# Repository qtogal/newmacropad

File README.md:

# newmacropad
This is my first macropad and my first time making a custom pcb. This macropad case comes with a stand so you can use it sort of like a stream deck. 

The case has a stand at the bottom, making the angle adjustable. 

# BOM
- 4x Cherry MX Switches
- 4x any Keycap
- 4x M3x5x4 Heatset inserts
- 4x M3x16mm SHCS Bolts
- 16x 1N4148 DO-35 Diodes.
- 1x 0.91" 128x32 OLED Display
- 1x XIAO RP2040
- 1x Case (2 prints, 1 of them have 3 print in place parts)

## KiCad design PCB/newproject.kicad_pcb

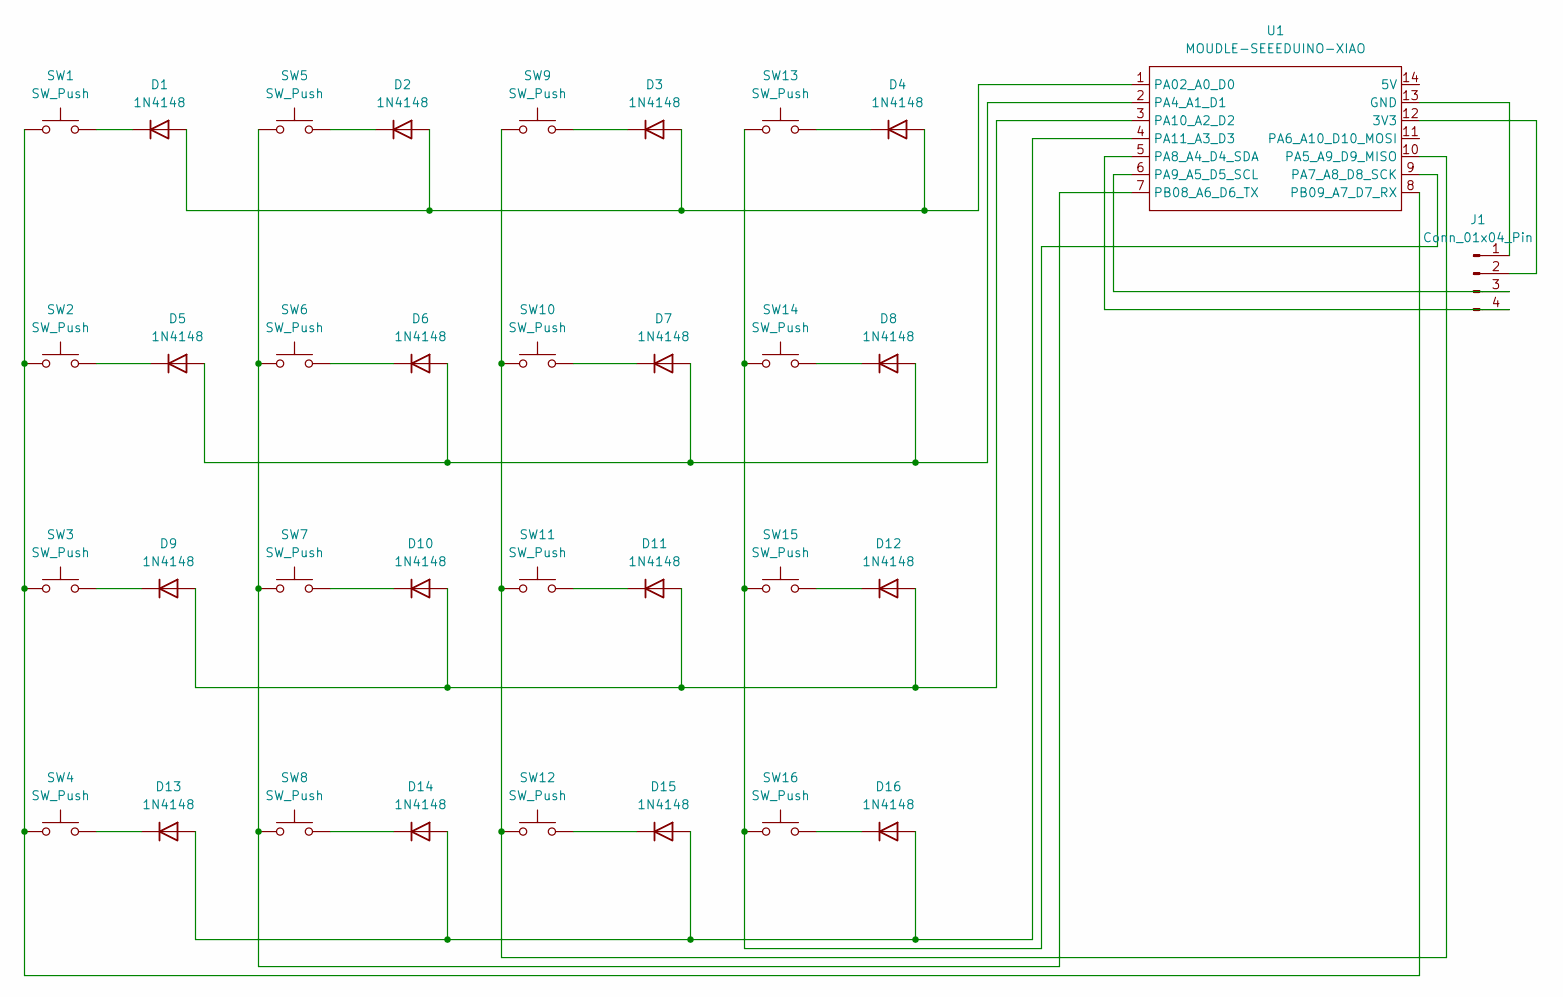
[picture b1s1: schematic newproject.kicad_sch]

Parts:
D1, D2, D3, D4, D5, D6, D7, D8, D9, D10, D11, D12, D13, D14, D15, D16: 1N4148; D_DO-35_SOD27_P7.62mm_Horizontal
J1: Conn_01x04_Pin; ER_OLEDM0.91_1x-I2C
SW1, SW2, SW3, SW4, SW5, SW6, SW7, SW8, SW9, SW10, SW11, SW12, SW13, SW14, SW15, SW16: SW_Push; SW_Cherry_MX_1.00u_PCB
U1: MOUDLE-SEEEDUINO-XIAO; XIAO-Generic-Hybrid-14P-2.54-21X17.8MM

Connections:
unnamed: D1.2 (A), D2.2 (A), D3.2 (A), D4.2 (A), U1.1 (PA02_A0_D0)
unnamed: D1.1 (K), SW1.2
unnamed: D2.1 (K), SW5.2
unnamed: D3.1 (K), SW9.2
unnamed: D4.1 (K), SW13.2
unnamed: D5.2 (A), D6.2 (A), D7.2 (A), D8.2 (A), U1.2 (PA4_A1_D1)
unnamed: D5.1 (K), SW2.2
unnamed: D6.1 (K), SW6.2
unnamed: D7.1 (K), SW10.2
unnamed: D8.1 (K), SW14.2
unnamed: D9.1 (K), SW3.2
unnamed: D9.2 (A), D10.2 (A), D11.2 (A), D12.2 (A), U1.3 (PA10_A2_D2)
unnamed: D10.1 (K), SW7.2
unnamed: D11.1 (K), SW11.2
unnamed: D12.1 (K), SW15.2
unnamed: D13.2 (A), D14.2 (A), D15.2 (A), D16.2 (A), U1.4 (PA11_A3_D3)
unnamed: D13.1 (K), SW4.2
unnamed: D14.1 (K), SW8.2
unnamed: D15.1 (K), SW12.2
unnamed: D16.1 (K), SW16.2
unnamed: J1.1, U1.13 (GND)
unnamed: J1.2, U1.12 (3V3)
unnamed: J1.3, U1.6 (PA9_A5_D5_SCL)
unnamed: J1.4, U1.5 (PA8_A4_D4_SDA)
unnamed: SW9.1, SW10.1, SW11.1, SW12.1, U1.10 (PA5_A9_D9_MISO)
unnamed: SW13.1, SW14.1, SW15.1, SW16.1, U1.9 (PA7_A8_D8_SCK)
unnamed: SW5.1, SW6.1, SW7.1, SW8.1, U1.7 (PB08_A6_D6_TX)
unnamed: SW1.1, SW2.1, SW3.1, SW4.1, U1.8 (PB09_A7_D7_RX)

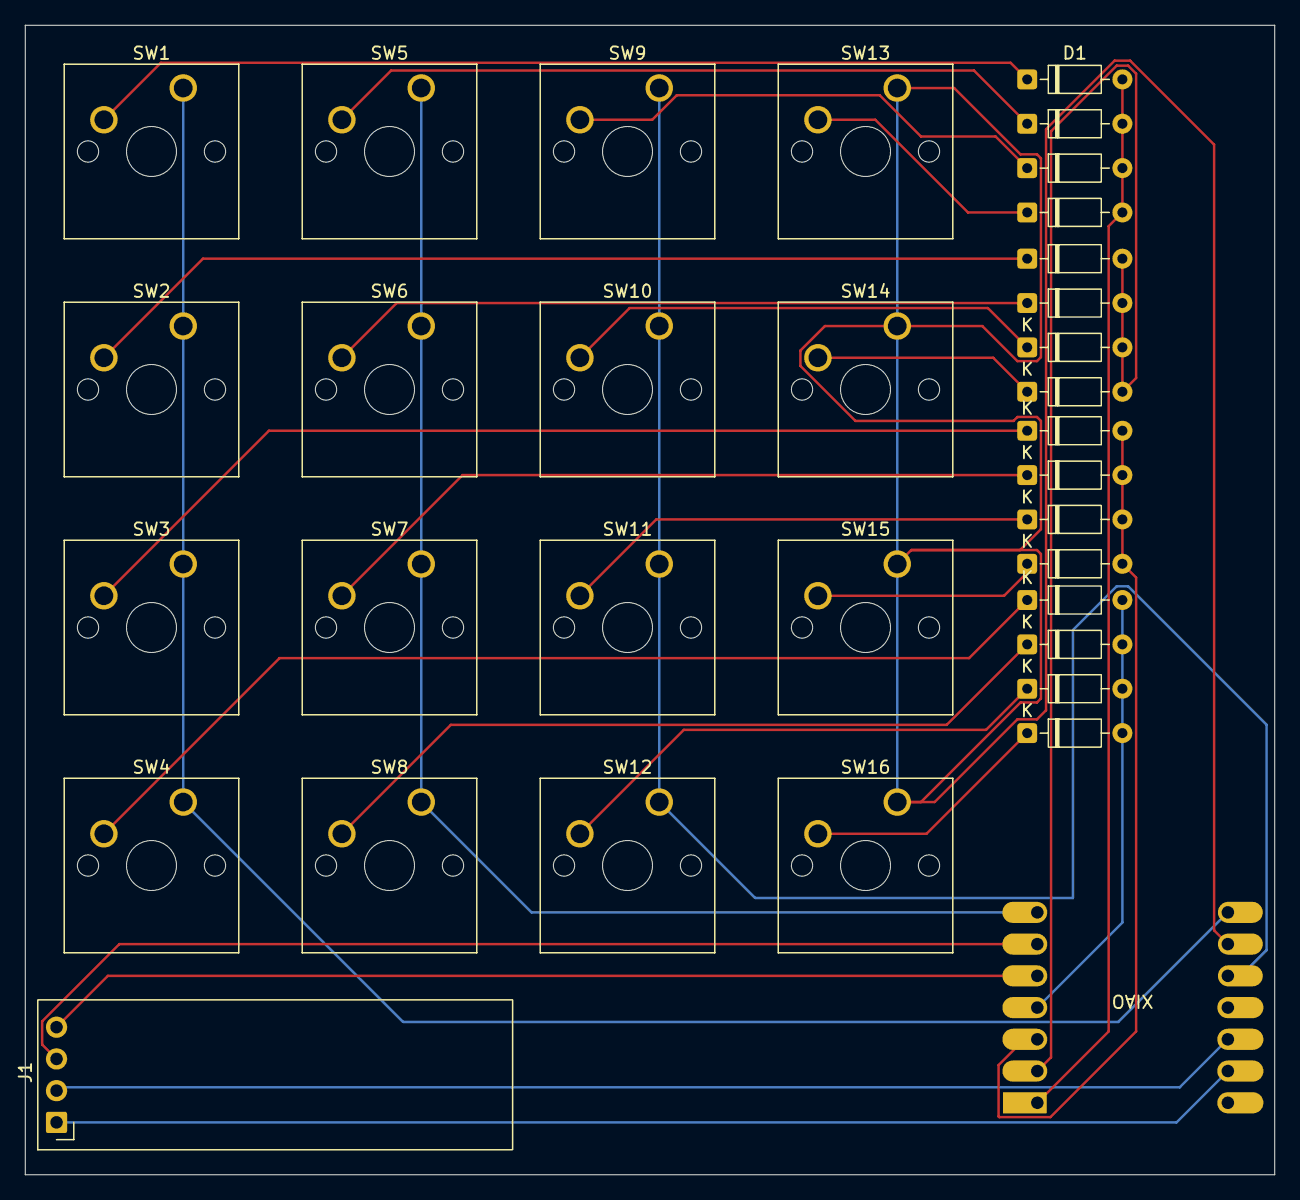
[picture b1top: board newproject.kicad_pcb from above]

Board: 2 copper layers, 100.0 x 92.0 mm, 34 parts (1 on the bottom side), 28 nets.
